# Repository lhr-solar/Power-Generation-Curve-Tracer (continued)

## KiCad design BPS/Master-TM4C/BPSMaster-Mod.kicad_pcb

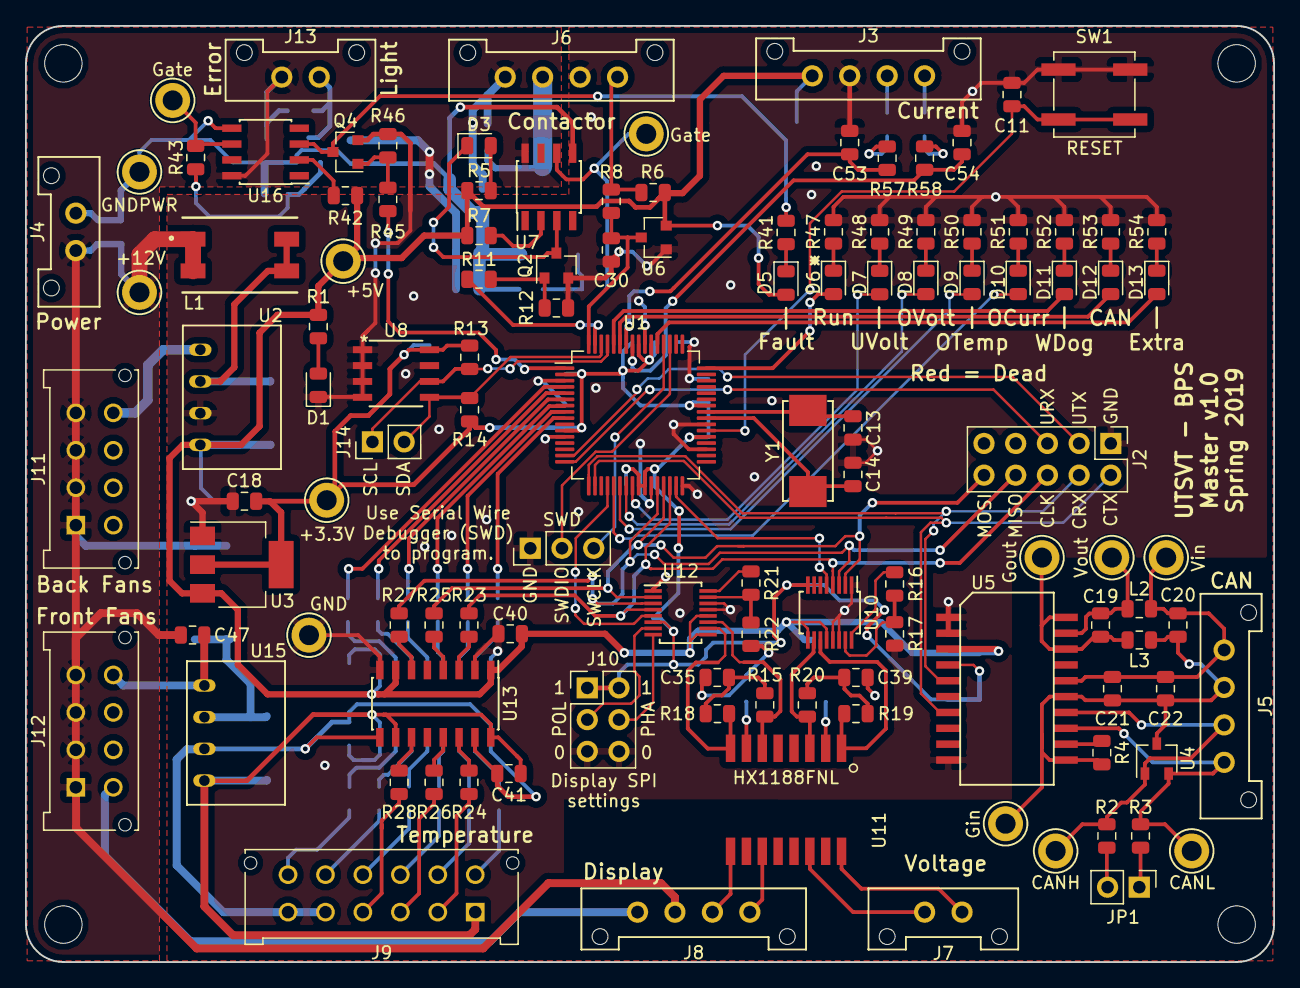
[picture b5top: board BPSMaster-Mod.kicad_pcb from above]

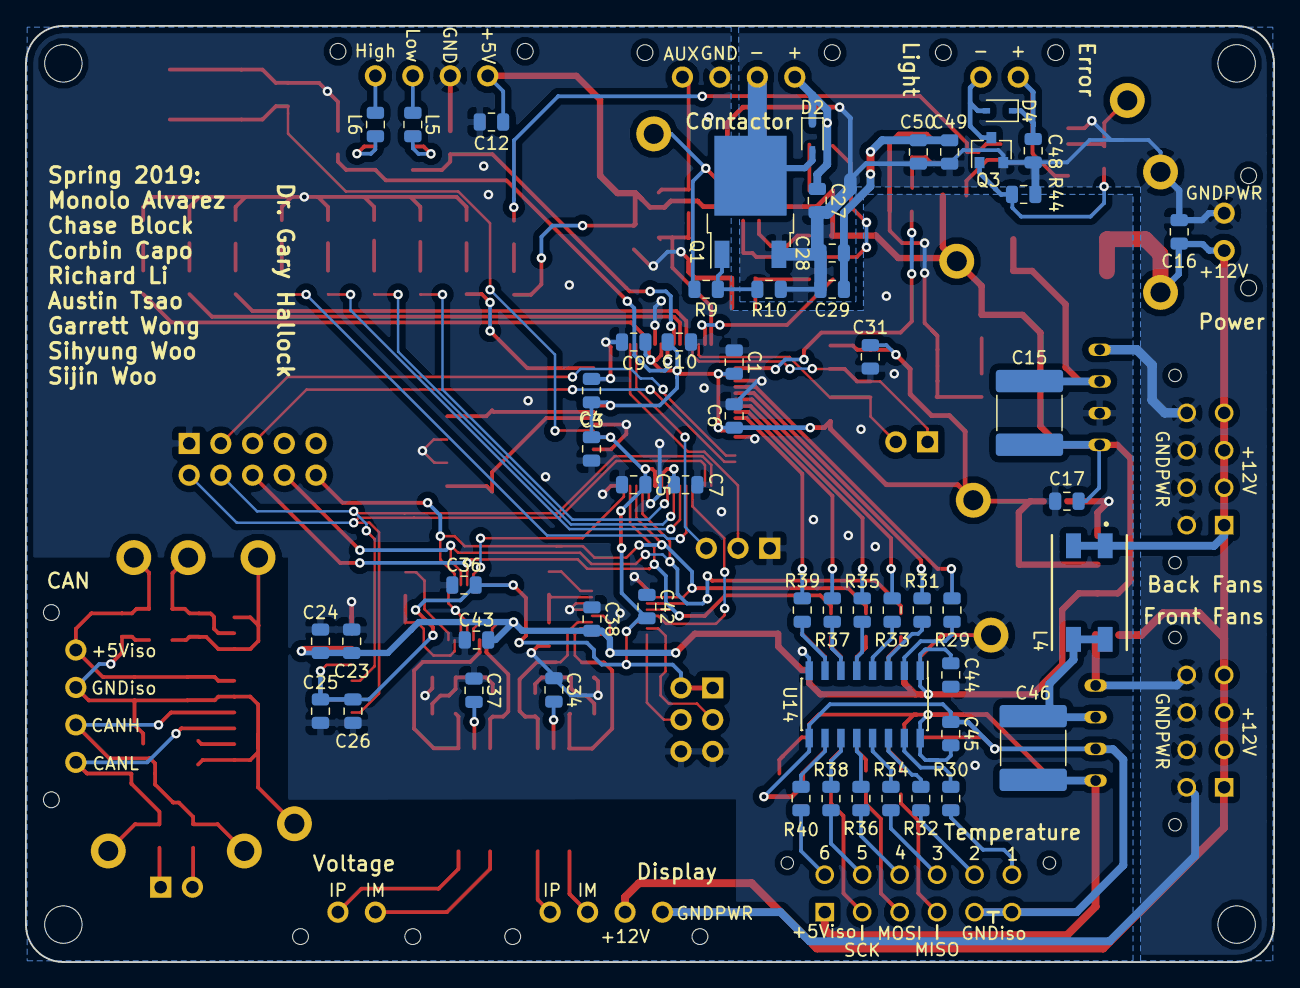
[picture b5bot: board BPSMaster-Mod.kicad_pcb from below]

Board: 2 copper layers, 100.0 x 75.0 mm, 176 parts (55 on the bottom side), 126 nets.

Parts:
C1, C3, C4, C5, C6, C9, C11, C12, C21, C24, C25, C29, C31, C36, C38, C40, C41, C42, C43, C44, C45, C50: 0.1uF; C_0805_2012Metric
C7, C16, C47: 4.7uF; C_0805_2012Metric
C10, C27, C30, C48, C53, C54: 1uF; C_0805_2012Metric
C13, C14: 6pF; C_0805_2012Metric
C15, C46: 470pF; C_2220_5650Metric
C17, C18, C20, C23, C28, C49: 10uF; C_0805_2012Metric
C19: 0.22uF; C_0805_2012Metric
C22, C26, C34, C35, C37, C39: 0.01uF; C_0805_2012Metric
D1: PowerOn; LED_0805_2012Metric
D2, D4: 1N4148WS; D_SOD-323
D3: ContactorEn; LED_0805_2012Metric
D5: Fault; LED_0805_2012Metric
D6: Heartbeat; LED_0805_2012Metric
D7: UVolt; LED_0805_2012Metric
D8: OVolt; LED_0805_2012Metric
D9: OTemp; LED_0805_2012Metric
D10: OCurr; LED_0805_2012Metric
D11: WDError; LED_0805_2012Metric
D12: CANError; LED_0805_2012Metric
D13: Extra; LED_0805_2012Metric
J1: SWD; PinHeader_1x03_P2.54mm_Vertical
J2: Logic Analyzer; PinHeader_2x05_P2.54mm_Vertical
J3: CurrentSlaveConnector; Molex_MicroFit3.0_1x4xP3.00mm_PolarizingPeg_Vertical
J4: CarPowerConnector; Molex_MicroFit3.0_1x2xP3.00mm_PolarizingPeg_Vertical
J5: CAN_Out; Molex_MicroFit3.0_1x4xP3.00mm_PolarizingPeg_Vertical
J6: ContactorConnector; Molex_MicroFit3.0_1x4xP3.00mm_PolarizingPeg_Vertical
J7: VoltageSlaveConnector; Molex_MicroFit3.0_1x2xP3.00mm_PolarizingPeg_Vertical
J8: DisplayConnector; Molex_MicroFit3.0_1x4xP3.00mm_PolarizingPeg_Vertical
J9: TempSlaveConnector; Molex_MicroFit3.0_2x6xP3.00mm_PolarizingPeg_Vertical
J10: DisplayJumper; PinHeader_2x03_P2.54mm_Vertical
J11: FrontFans; Molex_MicroFit3.0_2x4xP3.00mm_PolarizingPeg_Vertical
J12: BackFans; Molex_MicroFit3.0_2x4xP3.00mm_PolarizingPeg_Vertical
J13: ErrorLightConnector; Molex_MicroFit3.0_1x2xP3.00mm_PolarizingPeg_Vertical
J14: Conn_01x03; PinHeader_1x02_P2.54mm_Vertical
JP1: Termination Resistors; PinHeader_1x02_P2.54mm_Vertical
L1, L4: 10uH; SRF0905A
L2, L3: 2kH; L_0805_2012Metric
L5, L6: 600; L_0805_2012Metric
MH1, MH2, MH3, MH4: MountingHole; MountingHole_3mm
Q1: VND5N07-E; TO-252-2
Q2, Q3, Q4: NTR4003NT1G; SOT-23
R1, R5: 1.5k; R_0805_2012Metric
R2, R3: 60; R_0805_2012Metric
R4, R9, R11, R43, R45: 0; R_0805_2012Metric
R6, R13, R14: 4.7k; R_0805_2012Metric
R7, R42: 470; R_0805_2012Metric
R8: 1k; R_0805_2012Metric
R10, R12, R44, R46: 10k; R_0805_2012Metric
R15, R18, R19, R20: 49.9; R_0805_2012Metric
R16, R21: 806; R_0805_2012Metric
R17, R22: 1.21k; R_0805_2012Metric
R23, R24, R25, R26, R27, R28, R29, R30, R31, R32, R33, R34, R35, R36, R37, R38, R39, R40: 50; R_0805_2012Metric
R41: 1.6k; R_0805_2012Metric
R47: 680; R_0805_2012Metric
R48, R49, R50, R51, R52, R53, R54: 750; R_0805_2012Metric
R57, R58: 220k; R_0805_2012Metric
SW1: B3SL-1002P; SW_SPST_B3SL-1002P
TP1: +12V_TP; TestPoint_Keystone_5005-5009_Compact
TP2: +5V_TP; TestPoint_Keystone_5005-5009_Compact
TP3: GND_TP; TestPoint_Keystone_5005-5009_Compact
TP4: +3.3V_TP; TestPoint_Keystone_5005-5009_Compact
TP5: CAN_ISO_Vout; TestPoint_Keystone_5005-5009_Compact
TP6: CAN_ISO_Vin; TestPoint_Keystone_5005-5009_Compact
TP7: CAN_ISO_GndIn; TestPoint_Keystone_5005-5009_Compact
TP8: CAN_ISO_GndOut; TestPoint_Keystone_5005-5009_Compact
TP9: CAN_H; TestPoint_Keystone_5005-5009_Compact
TP12: CAN_L; TestPoint_Keystone_5005-5009_Compact
TP13: ContactorGate_TP; TestPoint_Keystone_5005-5009_Compact
TP14: StrobeLightGate_TP; TestPoint_Keystone_5005-5009_Compact
TP15: GNDPWR_TP; TestPoint_Keystone_5005-5009_Compact
U1: TM4C123GH6PM; LQFP-64_10x10mm_P0.5mm
U2, U15: RI3-1205S; RI3_DC_Converter
U3: NCP1117-3.3_SOT223; SOT-223-3_TabPin2
U4: CDSOT23-T24CAN; SOT-23W
U5: ADM3055E; SOIC-20W_7.5x15.4mm_Pitch1.27mm
U6: BAS70-04; SOT-23
U7, U16: SI8261ABC-IS; SOIC-8_3.9x4.9mm_P1.27mm
U8: M24128; M24128-BRMN6P
U10, U12: LTC6820; MSOP-16_3x4mm_P0.5mm
U11: HX1188FNL; HXXXX
U13: Si8641EC-B-IS1; SOIC-16_3.9x9.9mm_P1.27mm
U14: SI8660EC-B-IS1; SOIC-16_3.9x9.9mm_P1.27mm
Y1: NX8045GB-8.000M-STD-CSJ-1

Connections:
+3V3: C1.1, C3.1, C4.1, C5.1, C6.1, C7.1, C9.1, C10.1, C18.1, C25.1, C26.1, C31.1, C36.1, C42.1, J10.1, J10.2, R13.1, R14.1, TP4.1, U1.2, U1.11, U1.25, U1.26, U1.37, U1.42, U1.54, U1.56, U3.2, U5.4, U8.8, U10.6, U10.7, U10.8, U12.6
+5V: C12.2, C15.2, C17.1, C23.1, C24.1, C38.1, C40.1, C43.1, C44.1, D5.2, J3.1, R1.1, R5.1, R6.2, R7.2, R42.2, TP2.1, U2.4, U3.3, U5.3, U6.2, U10.9, U10.12, U12.9, U12.12, U13.1, U13.7, U14.1
+5VL: C41.1, C45.1, C46.2, J9.1, U13.10, U13.16, U14.16, U15.4
+12V: C16.1, C27.2, C28.1, C29.1, C47.1, C48.2, C49.1, C50.1, D2.1, D4.1, J4.1, J6.1, J8.3, J11.1, J11.2, J11.3, J11.4, J12.1, J12.2, J12.3, J12.4, J13.1, L1.1, L1.2, L4.1, L4.2, TP1.1, U7.8, U16.8
/AIN10: C53.1, R57.2, U1.58
/AIN11: C54.1, R58.2, U1.57
/CAN1_RX: J2.4, U1.17, U5.5
/CAN1_TX: J2.2, U1.18, U5.7
/CAN/CAN_H: J5.3, R2.2, TP9.1, U4.1, U5.14
/CAN/CAN_L: J5.4, R3.2, TP12.1, U4.2, U5.13
/CAN/RSlope: R4.1, U5.12
/CAN/TERM_H: JP1.2, R2.1
/CAN/TERM_L: JP1.1, R3.1
/Contactor Driver/CONTACTOR_V-: D2.2, J6.2, Q1.2
/DISPLAY_CS: U1.20, U12.5
/FAULT: R45.2, U1.1
/I2C3_SCL: J14.1, R13.2, U1.61, U8.6
/I2C3_SDA: J14.2, R14.2, U1.62, U8.5
/LTC6811_CS: U1.31, U10.5
/NRST: C11.1, SW1.1, U1.38
/OSC_IN: C14.1, U1.40, Y1.2
/OSC_OUT: C13.1, U1.41, Y1.1
/PA4: D10.2, U1.21
/PA5: D9.2, U1.22
/PA6: D8.2, U1.23
/PA7: D7.2, U1.24
/PD2: R11.2, U1.63
/PD3: C30.1, R8.1, U1.64, U6.3
/PD6: D13.2, U1.53
/PE4: D12.2, U1.59
/PE5: D11.2, U1.60
/RUN: D6.2, U1.48
/SPI1_CLK: J2.6, R23.2, U1.30, U10.4, U12.4
/SPI1_MISO: J2.8, R27.2, U1.28, U10.3, U12.3
/SPI1_MOSI: J2.10, R25.2, U1.29, U10.2, U12.2
/SPI/CS1: J9.12, R30.1
/SPI/CS2: J9.11, R32.1
/SPI/CS3: J9.10, R34.1
/SPI/CS4: J9.9, R36.1
/SPI/CS5: J9.8, R38.1
/SPI/CS6: J9.7, R40.1
/SPI/DISP_IM: R18.1, U11.8, U12.10
/SPI/DISP_IP: R15.1, U11.6, U12.11
/SPI/DISP_PHA: J10.4, U12.8
/SPI/DISP_POL: J10.3, U12.7
/SPI/VOLT_IM: R20.1, U10.10, U11.3
/SPI/VOLT_IP: R19.1, U10.11, U11.1
/SWCLK: J1.3, U1.52
/SWDIO: J1.2, U1.51
/TEMP_CS1: R29.1, U1.4
/TEMP_CS2: R31.1, U1.5
/TEMP_CS3: R33.1, U1.6
/TEMP_CS4: R35.1, U1.7
/TEMP_CS5: R37.1, U1.8
/TEMP_CS6: R39.1, U1.9
/UART1_RX: J2.5, U1.16
/UART1_TX: J2.3, U1.15
GND: C1.2, C3.2, C4.2, C5.2, C6.2, C7.2, C9.2, C10.2, C11.2, C12.1, C13.2, C14.2, C17.2, C18.2, C23.2, C24.2, C25.2, C26.2, C30.2, C31.2, C34.2, C35.2, C36.2, C37.2, C38.2, C39.2, C40.2, C42.2, C43.2, C44.2, C53.2, C54.2, D1.1, J1.1, J2.1, J3.2, J6.3, J10.5, J10.6, Q2.2, Q4.2, R12.2, R17.1, R22.1, R46.2, R47.2, R48.2, R49.2, R50.2, R51.2, R52.2, R53.2, R54.2, SW1.2, TP3.1, U1.3, U1.12, U1.27, U1.32, U1.35, U1.39, U1.55, U2.3, U3.1, U5.1, U5.2, U5.10, U6.1, U8.1, U8.2, U8.3, U8.4, U8.7, U10.1, U10.13, U10.14, U12.1, U12.13, U12.14, U13.2, U13.8, U14.8
GNDPWR: C16.2, C27.1, C28.2, C29.2, C47.2, C48.1, C49.2, C50.2, J4.2, J8.4, J11.5, J11.6, J11.7, J11.8, J12.5, J12.6, J12.7, J12.8, Q1.3, Q3.2, R10.2, R44.2, TP15.1, U2.1, U7.5, U15.1, U16.5
GND_A: C41.2, C45.2, J9.5, J9.6, U13.9, U13.15, U14.9, U15.3
unnamed: C15.1, L1.3, L1.4, U2.2
unnamed: C19.1, L2.2, TP5.1, U5.19
unnamed: C19.2, L3.2, TP8.1, U5.18, U5.20
unnamed: C20.1, C21.1, C22.1, J5.1, L2.1, TP6.1, U5.16
unnamed: C20.2, C21.2, C22.2, J5.2, L3.1, R4.2, TP7.1, U4.3, U5.11, U5.15
unnamed: C34.1, U11.7
unnamed: C35.1, R15.2, R18.2
unnamed: C37.1, U11.2
unnamed: C39.1, R19.2, R20.2
unnamed: C46.1, L4.3, L4.4, U15.2
unnamed: D1.2, R1.2
unnamed: D3.1, Q2.3, U7.3
unnamed: D3.2, R5.2
unnamed: D4.2, J13.2, Q3.3
unnamed: D5.1, R41.1
unnamed: D6.1, R47.1
unnamed: D7.1, R48.1
unnamed: D8.1, R49.1
unnamed: D9.1, R50.1
unnamed: D10.1, R51.1
unnamed: D11.1, R52.1
unnamed: D12.1, R53.1
unnamed: D13.1, R54.1
unnamed: J3.3, L5.1
unnamed: J3.4, L6.1
unnamed: J6.4, R6.1, R8.2
unnamed: J7.1, U11.16
unnamed: J7.2, U11.14
unnamed: J8.1, U11.11
unnamed: J8.2, U11.9
unnamed: J9.2, R24.2
unnamed: J9.3, R26.2
unnamed: J9.4, R28.2
unnamed: L5.2, R57.1
unnamed: L6.2, R58.1
unnamed: Q1.1, R9.1, R10.1
unnamed: Q2.1, R11.1, R12.1
unnamed: Q3.1, R43.1, R44.1
unnamed: Q4.1, R45.1, R46.1
unnamed: Q4.3, R41.2, U16.3
unnamed: R7.1, U7.2
unnamed: R9.2, TP13.1, U7.6
unnamed: R16.1, R17.2, U10.15
unnamed: R16.2, U10.16
unnamed: R21.1, R22.2, U12.15
unnamed: R21.2, U12.16
unnamed: R23.1, U13.3
unnamed: R24.1, U13.14
unnamed: R25.1, U13.4
unnamed: R26.1, U13.13
unnamed: R27.1, U13.6
unnamed: R28.1, U13.11
unnamed: R29.2, U14.2
unnamed: R30.2, U14.15
unnamed: R31.2, U14.3
unnamed: R32.2, U14.14
unnamed: R33.2, U14.4
unnamed: R34.2, U14.13
unnamed: R35.2, U14.5
unnamed: R36.2, U14.12
unnamed: R37.2, U14.6
unnamed: R38.2, U14.11
unnamed: R39.2, U14.7
unnamed: R40.2, U14.10
unnamed: R42.1, U16.2
unnamed: R43.2, TP14.1, U16.6

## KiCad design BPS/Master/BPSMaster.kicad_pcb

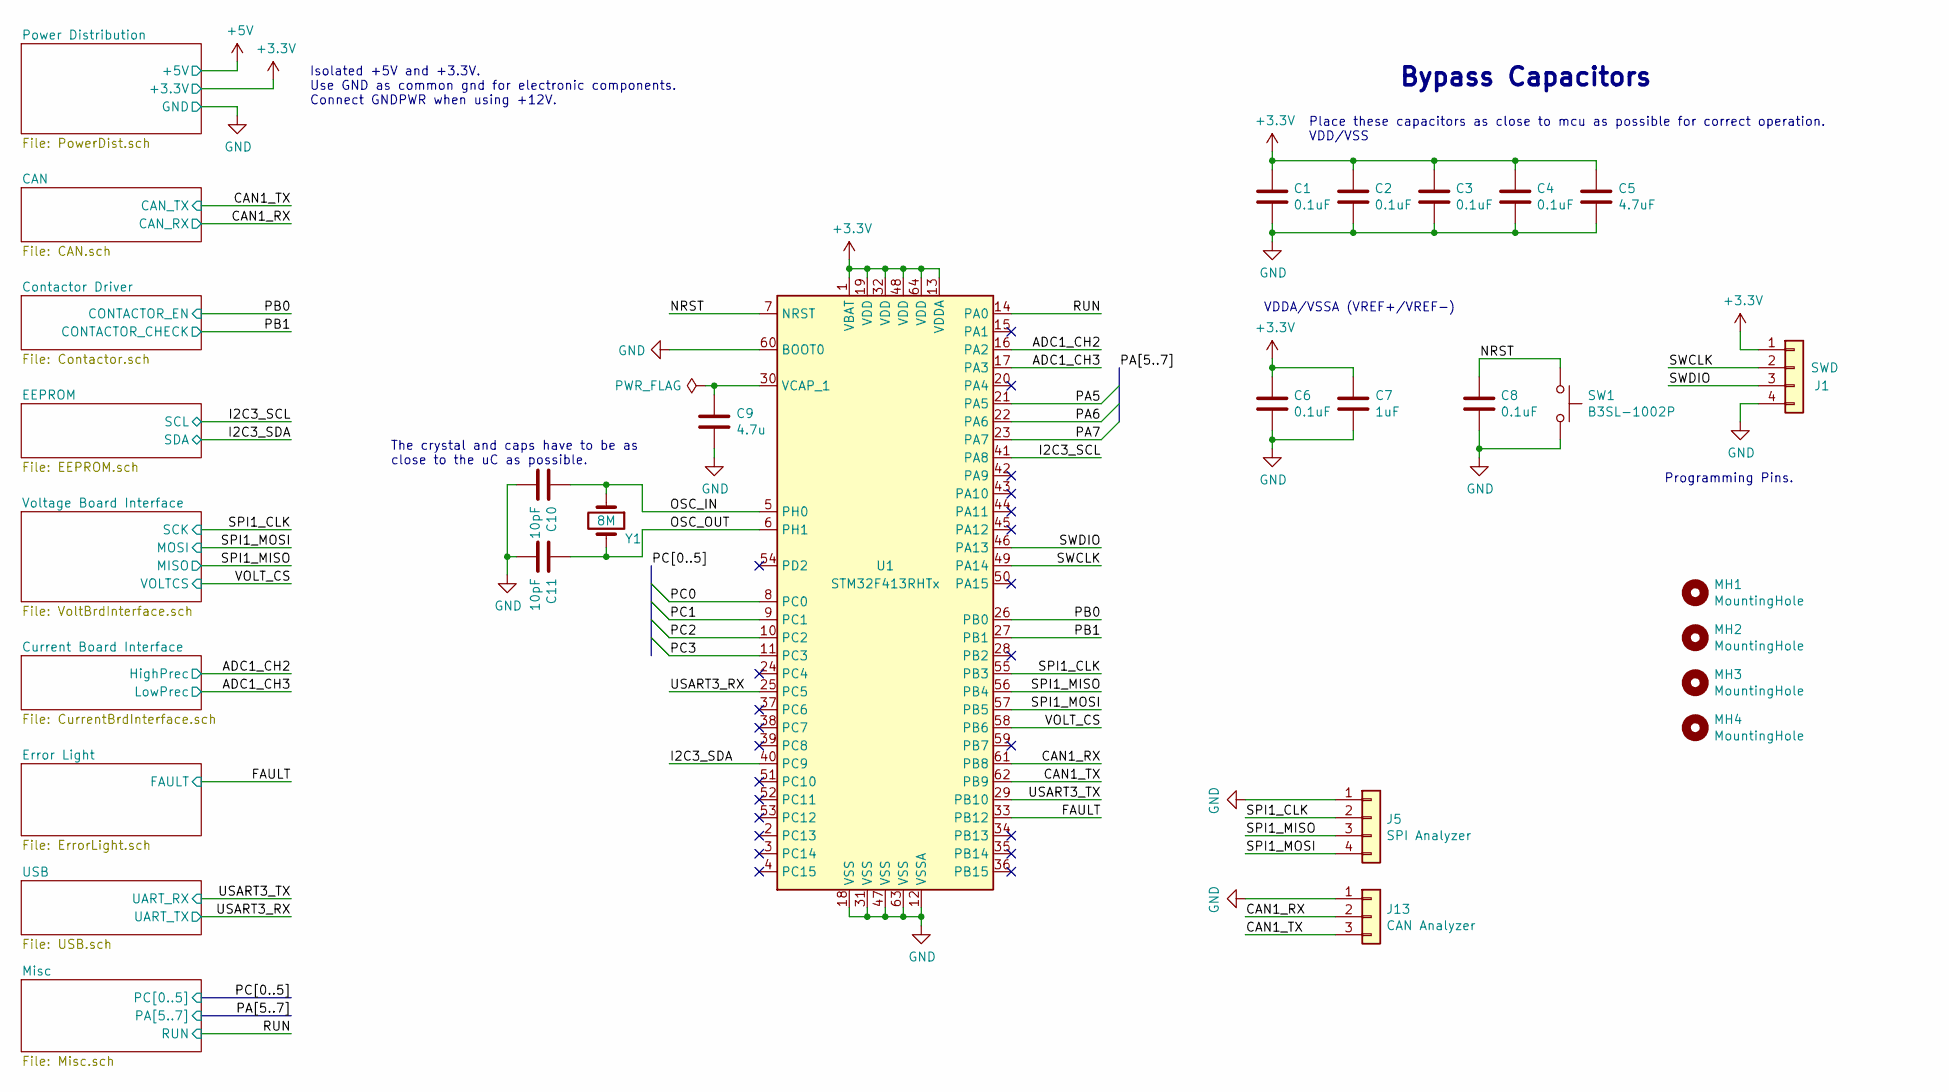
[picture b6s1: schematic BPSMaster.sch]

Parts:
C1, C2, C3, C4, C6, C8: 0.1uF; C_0805_2012Metric
C5: 4.7uF; C_0805_2012Metric
C7: 1uF; C_0805_2012Metric
C9: 4.7u; C_0805_2012Metric
C10, C11: 10pF; C_0805_2012Metric
J1: SWD; PinHeader_1x04_P2.54mm_Vertical
J5: SPI Analyzer; PinHeader_1x04_P2.54mm_Vertical
J13: CAN Analyzer; PinHeader_1x03_P2.54mm_Vertical
MH1, MH2, MH3, MH4: MountingHole; MountingHole_3mm
SW1: B3SL-1002P; SW_SPST_B3SL-1002P
U1: STM32F413RHTx; LQFP-64_10x10mm_P0.5mm
Y1: 8M; Crystal_SMD_TXC_7A-2Pin_5x3.2mm

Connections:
+3V3: C1.1, C2.1, C3.1, C4.1, C5.1, C6.1, C7.1, J1.1, U1.1 (VBAT), U1.13 (VDDA), U1.19 (VDD), U1.32 (VDD), U1.48 (VDD), U1.64 (VDD); also elsewhere on the board
/ADC1_CH2: U1.16 (PA2); also elsewhere on the board
/ADC1_CH3: U1.17 (PA3); also elsewhere on the board
/CAN1_RX: J13.2, U1.61 (PB8); also elsewhere on the board
/CAN1_TX: J13.3, U1.62 (PB9); also elsewhere on the board
/FAULT: U1.33 (PB12); also elsewhere on the board
/I2C3_SCL: U1.41 (PA8); also elsewhere on the board
/I2C3_SDA: U1.40 (PC9); also elsewhere on the board
/NRST: C8.1, SW1.1, U1.7 (NRST)
/OSC_IN: C10.1, U1.5 (PH0), Y1.1
/OSC_OUT: C11.1, U1.6 (PH1), Y1.2
/PA5: U1.21 (PA5); also elsewhere on the board
/PA6: U1.22 (PA6); also elsewhere on the board
/PA7: U1.23 (PA7); also elsewhere on the board
/PB0: U1.26 (PB0); also elsewhere on the board
/PB1: U1.27 (PB1); also elsewhere on the board
/PC0: U1.8 (PC0); also elsewhere on the board
/PC1: U1.9 (PC1); also elsewhere on the board
/PC2: U1.10 (PC2); also elsewhere on the board
/PC3: U1.11 (PC3); also elsewhere on the board
/RUN: U1.14 (PA0); also elsewhere on the board
/SPI1_CLK: J5.2, U1.55 (PB3); also elsewhere on the board
/SPI1_MISO: J5.3, U1.56 (PB4); also elsewhere on the board
/SPI1_MOSI: J5.4, U1.57 (PB5); also elsewhere on the board
/SWCLK: J1.2, U1.49 (PA14)
/SWDIO: J1.3, U1.46 (PA13)
/USART3_RX: U1.25 (PC5); also elsewhere on the board
/USART3_TX: U1.29 (PB10); also elsewhere on the board
/VOLT_CS: U1.58 (PB6); also elsewhere on the board
GND: C1.2, C2.2, C3.2, C4.2, C5.2, C6.2, C7.2, C8.2, C9.2, C10.2, C11.2, J1.4, J5.1, J13.1, SW1.2, U1.12 (VSSA), U1.18 (VSS), U1.31 (VSS), U1.47 (VSS), U1.60 (BOOT0), U1.63 (VSS); also elsewhere on the board
unnamed: C9.1, U1.30 (VCAP_1)

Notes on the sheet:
Place these capacitors as close to mcu as possible for correct operation. VDD/VSS
VDDA/VSSA (VREF+/VREF-)
Isolated +5V and +3.3V. Use GND as common gnd for electronic components. Connect GNDPWR when using +12V.
The crystal and caps have to be as close to the uC as possible.
Programming Pins.
Bypass Capacitors

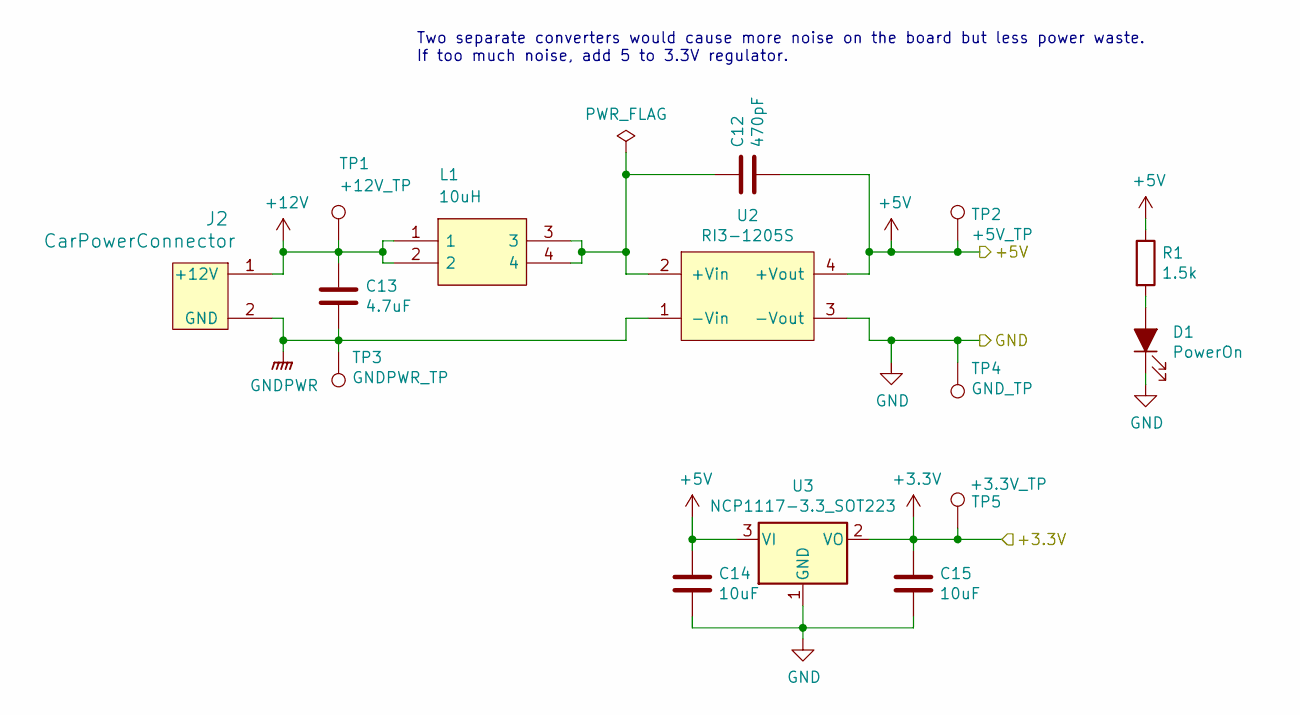
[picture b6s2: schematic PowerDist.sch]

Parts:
C12: 470pF; C_2220_5650Metric; Rating 4kV
C13: 4.7uF; C_0805_2012Metric
C14, C15: 10uF; C_0805_2012Metric
D1: PowerOn; LED_0805_2012Metric
J2: CarPowerConnector; Molex_MicroFit3.0_1x2xP3.00mm_PolarizingPeg_Vertical
L1: 10uH; SRF0905A
R1: 1.5k; R_0805_2012Metric
TP1: +12V_TP; TestPoint_Keystone_5005-5009_Compact
TP2: +5V_TP; TestPoint_Keystone_5005-5009_Compact
TP3: GNDPWR_TP; TestPoint_Keystone_5005-5009_Compact
TP4: GND_TP; TestPoint_Keystone_5005-5009_Compact
TP5: +3.3V_TP; TestPoint_Keystone_5005-5009_Compact
U2: RI3-1205S; RI3_DC_Converter
U3: NCP1117-3.3_SOT223; SOT-223-3_TabPin2

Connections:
+3V3: C15.1, TP5.1, U3.2 (VO); also elsewhere on the board
+5V: C12.2, C14.1, R1.1, TP2.1, U2.4 (+Vout), U3.3 (VI); also elsewhere on the board
+12V: C13.1, J2.1 (+12V), L1.1, L1.2, TP1.1; also elsewhere on the board
GND: C14.2, C15.2, D1.1 (K), TP4.1, U2.3 (-Vout), U3.1 (GND); also elsewhere on the board
GNDPWR: C13.2, J2.2 (GND), TP3.1, U2.1 (-Vin); also elsewhere on the board
unnamed: C12.1, L1.3, L1.4, U2.2 (+Vin)
unnamed: D1.2 (A), R1.2

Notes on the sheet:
Two separate converters would cause more noise on the board but less power waste. If too much noise, add 5 to 3.3V regulator.

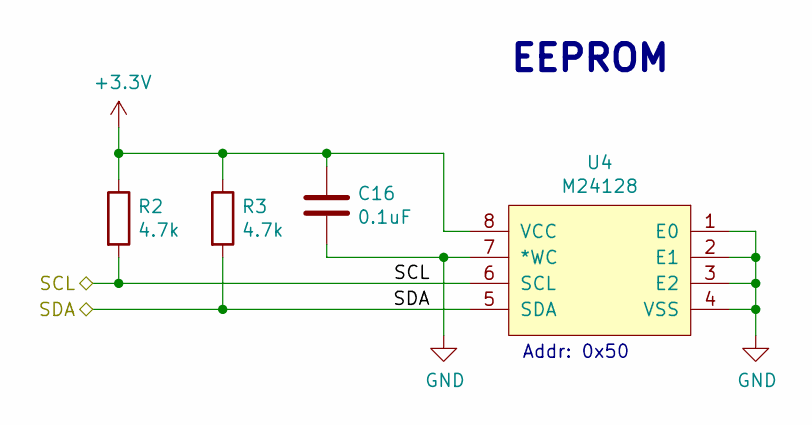
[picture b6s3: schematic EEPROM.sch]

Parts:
C16: 0.1uF; C_0805_2012Metric
R2, R3: 4.7k; R_0805_2012Metric
U4: M24128; M24128-BRMN6P

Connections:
+3V3: C16.1, R2.1, R3.1, U4.8 (VCC); also elsewhere on the board
/I2C3_SCL: R2.2, U4.6 (SCL); also elsewhere on the board
/I2C3_SDA: R3.2, U4.5 (SDA); also elsewhere on the board
GND: C16.2, U4.1 (E0), U4.2 (E1), U4.3 (E2), U4.4 (VSS), U4.7 (*WC); also elsewhere on the board

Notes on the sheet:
EEPROM
Addr: 0x50

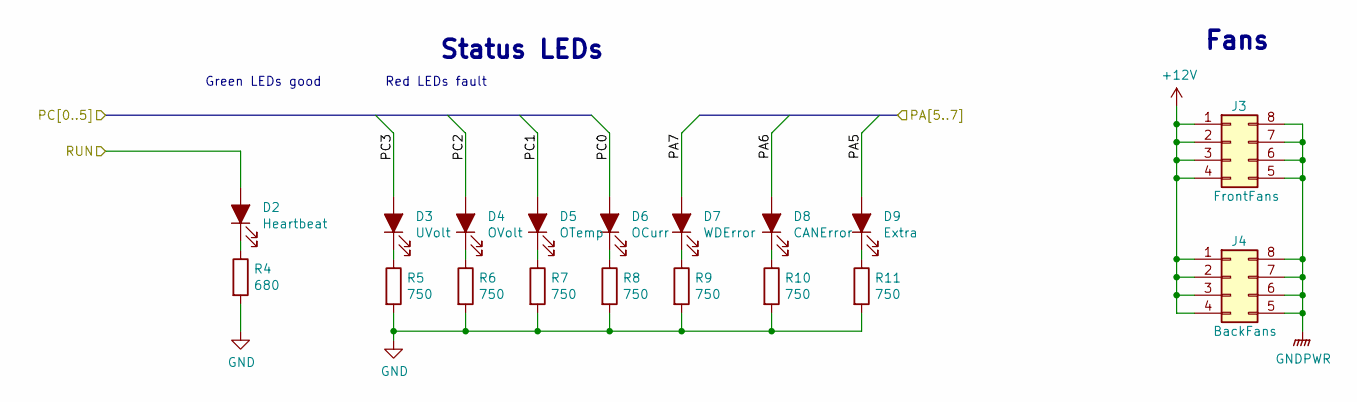
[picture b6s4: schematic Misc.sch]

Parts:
D2: Heartbeat; LED_0805_2012Metric
D3: UVolt; LED_0805_2012Metric
D4: OVolt; LED_0805_2012Metric
D5: OTemp; LED_0805_2012Metric
D6: OCurr; LED_0805_2012Metric
D7: WDError; LED_0805_2012Metric
D8: CANError; LED_0805_2012Metric
D9: Extra; LED_0805_2012Metric
J3: FrontFans; Molex_MicroFit3.0_2x4xP3.00mm_PolarizingPeg_Vertical
J4: BackFans; Molex_MicroFit3.0_2x4xP3.00mm_PolarizingPeg_Vertical
R4: 680; R_0805_2012Metric
R5, R6, R7, R8, R9, R10, R11: 750; R_0805_2012Metric

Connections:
+12V: J3.1, J3.2, J3.3, J3.4, J4.1, J4.2, J4.3, J4.4; also elsewhere on the board
/PA5: D9.2 (A); also elsewhere on the board
/PA6: D8.2 (A); also elsewhere on the board
/PA7: D7.2 (A); also elsewhere on the board
/PC0: D6.2 (A); also elsewhere on the board
/PC1: D5.2 (A); also elsewhere on the board
/PC2: D4.2 (A); also elsewhere on the board
/PC3: D3.2 (A); also elsewhere on the board
/RUN: D2.2 (A); also elsewhere on the board
GND: R4.2, R5.2, R6.2, R7.2, R8.2, R9.2, R10.2, R11.2; also elsewhere on the board
GNDPWR: J3.5, J3.6, J3.7, J3.8, J4.5, J4.6, J4.7, J4.8; also elsewhere on the board
unnamed: D2.1 (K), R4.1
unnamed: D3.1 (K), R5.1
unnamed: D4.1 (K), R6.1
unnamed: D5.1 (K), R7.1
unnamed: D6.1 (K), R8.1
unnamed: D7.1 (K), R9.1
unnamed: D8.1 (K), R10.1
unnamed: D9.1 (K), R11.1

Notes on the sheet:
Fans
Green LEDs good
Red LEDs fault
Status LEDs

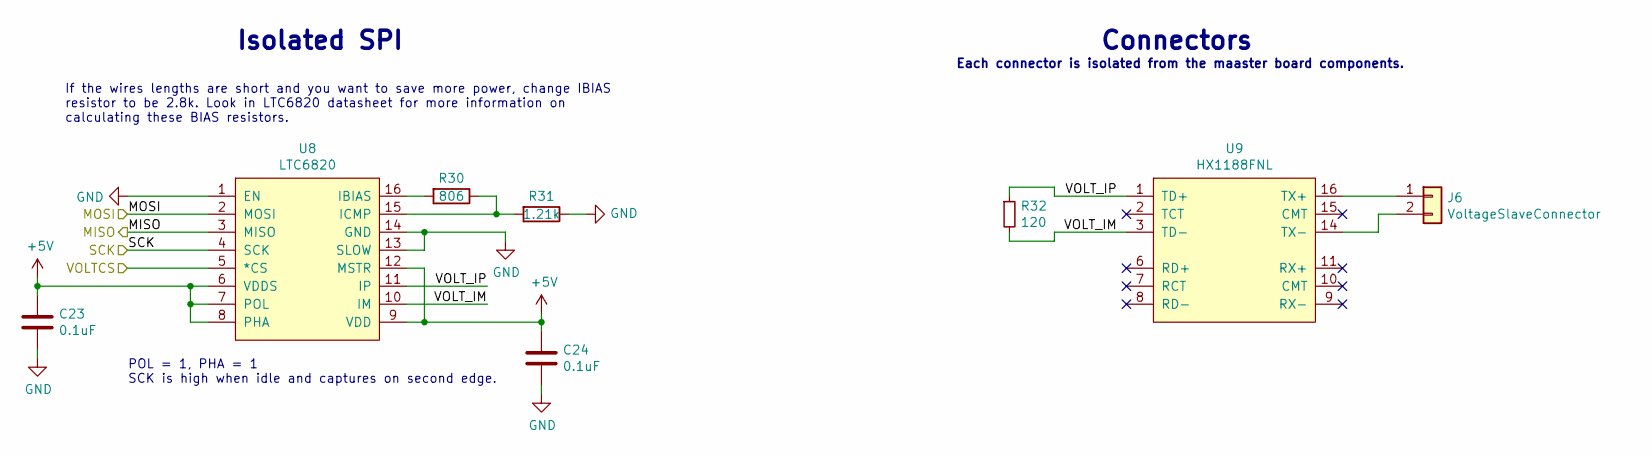
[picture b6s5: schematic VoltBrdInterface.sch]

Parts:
C23, C24: 0.1uF; C_0805_2012Metric
J6: VoltageSlaveConnector; Molex_MicroFit3.0_1x2xP3.00mm_PolarizingPeg_Vertical
R30: 806; R_0805_2012Metric
R31: 1.21k; R_0805_2012Metric
R32: 120; R_0805_2012Metric
U8: LTC6820; MSOP-16_3x4mm_P0.5mm
U9: HX1188FNL; HXXXX

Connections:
+5V: C23.1, C24.1, U8.6 (VDDS), U8.7 (POL), U8.8 (PHA), U8.9 (VDD), U8.12 (MSTR); also elsewhere on the board
/SPI1_CLK: U8.4 (SCK); also elsewhere on the board
/SPI1_MISO: U8.3 (MISO); also elsewhere on the board
/SPI1_MOSI: U8.2 (MOSI); also elsewhere on the board
/VOLT_CS: U8.5 (*CS); also elsewhere on the board
/Voltage Board Interface/VOLT_IM: R32.2, U8.10 (IM), U9.3 (TD-)
/Voltage Board Interface/VOLT_IP: R32.1, U8.11 (IP), U9.1 (TD+)
GND: C23.2, C24.2, R31.1, U8.1 (EN), U8.13 (SLOW), U8.14 (GND); also elsewhere on the board
unnamed: J6.1, U9.16 (TX+)
unnamed: J6.2, U9.14 (TX-)
unnamed: R30.1, R31.2, U8.15 (ICMP)
unnamed: R30.2, U8.16 (IBIAS)

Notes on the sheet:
POL = 1, PHA = 1 SCK is high when idle and captures on second edge.
If the wires lengths are short and you want to save more power, change IBIAS resistor to be 2.8k. Look in LTC6820 datasheet for more information on calculating these BIAS resistors.
Connectors
Each connector is isolated from the maaster board components.
Isolated SPI

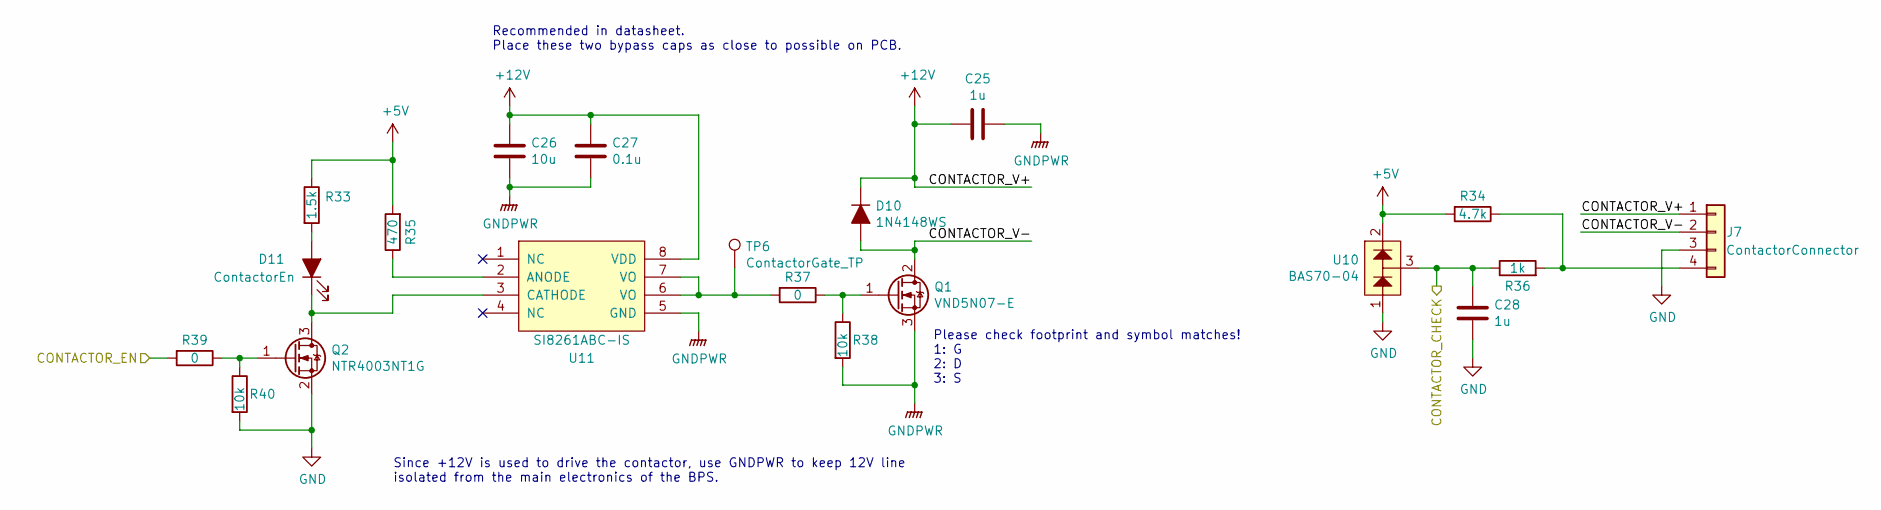
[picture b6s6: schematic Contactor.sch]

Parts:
C25, C28: 1u; C_0805_2012Metric
C26: 10u; C_0805_2012Metric
C27: 0.1u; C_0805_2012Metric
D10: 1N4148WS; D_SOD-323
D11: ContactorEn; LED_0805_2012Metric
J7: ContactorConnector; Molex_MicroFit3.0_1x4xP3.00mm_PolarizingPeg_Vertical
Q1: VND5N07-E; TO-252-2
Q2: NTR4003NT1G; SOT-23
R33: 1.5k; R_0805_2012Metric
R34: 4.7k; R_0805_2012Metric
R35: 470; R_0805_2012Metric
R36: 1k; R_0805_2012Metric
R37, R39: 0; R_0805_2012Metric
R38, R40: 10k; R_0805_2012Metric
TP6: ContactorGate_TP; TestPoint_Keystone_5005-5009_Compact
U10: BAS70-04; SOT-23
U11: SI8261ABC-IS; SOIC-8_3.9x4.9mm_P1.27mm

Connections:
+5V: R33.1, R34.2, R35.2, U10.2; also elsewhere on the board
+12V: C25.2, C26.1, C27.1, D10.1 (K), J7.1, U11.8 (VDD); also elsewhere on the board
/Contactor Driver/CONTACTOR_V-: D10.2 (A), J7.2, Q1.2 (D)
/PB0: R39.2; also elsewhere on the board
/PB1: C28.1, R36.1, U10.3; also elsewhere on the board
GND: C28.2, J7.3, Q2.2 (S), R40.2, U10.1; also elsewhere on the board
GNDPWR: C25.1, C26.2, C27.2, Q1.3 (S), R38.2, U11.5 (GND); also elsewhere on the board
unnamed: D11.1 (K), Q2.3 (D), U11.3 (CATHODE)
unnamed: D11.2 (A), R33.2
unnamed: J7.4, R34.1, R36.2
unnamed: Q1.1 (G), R37.1, R38.1
unnamed: Q2.1 (G), R39.1, R40.1
unnamed: R35.1, U11.2 (ANODE)
unnamed: R37.2, TP6.1, U11.6 (VO), U11.7 (VO)

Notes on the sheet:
Since +12V is used to drive the contactor, use GNDPWR to keep 12V line isolated from the main electronics of the BPS.
Recommended in datasheet. Place these two bypass caps as close to possible on PCB.
Please check footprint and symbol matches! 1: G 2: D 3: S

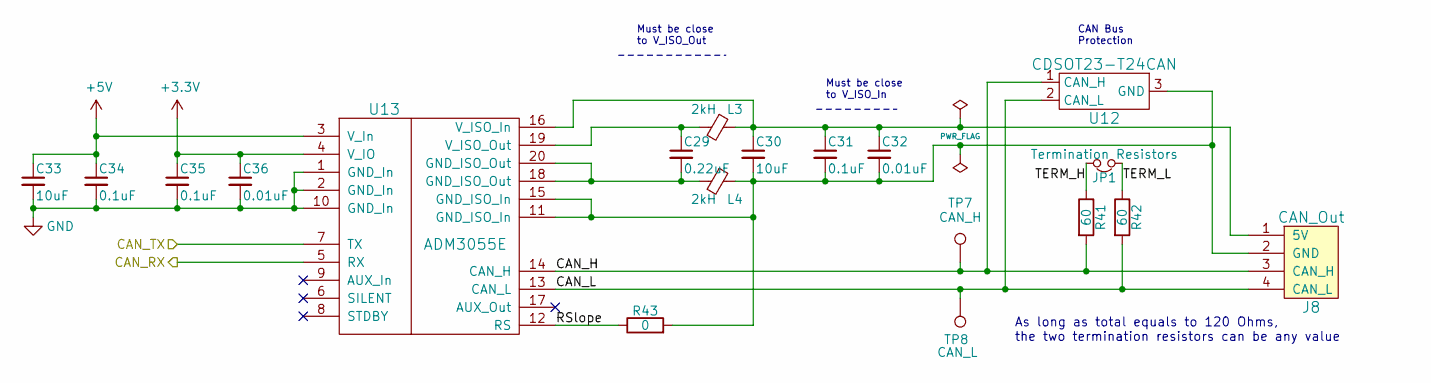
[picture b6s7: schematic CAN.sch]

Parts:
C29: 0.22uF; C_0805_2012Metric
C30, C33: 10uF; C_0805_2012Metric
C31, C34, C35: 0.1uF; C_0805_2012Metric
C32, C36: 0.01uF; C_0805_2012Metric
J8: CAN_Out; Molex_MicroFit3.0_1x4xP3.00mm_PolarizingPeg_Vertical
JP1: Termination Resistors; PinHeader_1x02_P2.54mm_Vertical
L3, L4: 2kH; L_0805_2012Metric
R41, R42: 60; R_0805_2012Metric
R43: 0; R_0805_2012Metric
TP7: CAN_H; TestPoint_Keystone_5005-5009_Compact
TP8: CAN_L; TestPoint_Keystone_5005-5009_Compact
U12: CDSOT23-T24CAN; SOT-23W
U13: ADM3055E; SOIC-20W_7.5x15.4mm_Pitch1.27mm

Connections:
+3V3: C35.1, C36.1, U13.4 (V_IO); also elsewhere on the board
+5V: C33.1, C34.1, U13.3 (V_In); also elsewhere on the board
/CAN1_RX: U13.5 (RX); also elsewhere on the board
/CAN1_TX: U13.7 (TX); also elsewhere on the board
/CAN/CAN_H: J8.3 (CAN_H), R41.2, TP7.1, U12.1 (CAN_H), U13.14 (CAN_H)
/CAN/CAN_L: J8.4 (CAN_L), R42.2, TP8.1, U12.2 (CAN_L), U13.13 (CAN_L)
/CAN/RSlope: R43.1, U13.12 (RS)
/CAN/TERM_H: JP1.2, R41.1
/CAN/TERM_L: JP1.1, R42.1
GND: C33.2, C34.2, C35.2, C36.2, U13.1 (GND_In), U13.2 (GND_In), U13.10 (GND_In); also elsewhere on the board
unnamed: C29.1, L3.2, U13.19 (V_ISO_Out)
unnamed: C29.2, L4.2, U13.18 (GND_ISO_Out), U13.20 (GND_ISO_Out)
unnamed: C30.1, C31.1, C32.1, J8.1 (5V), L3.1, U13.16 (V_ISO_In)
unnamed: C30.2, C31.2, C32.2, J8.2 (GND), L4.1, R43.2, U12.3 (GND), U13.11 (GND_ISO_In), U13.15 (GND_ISO_In)

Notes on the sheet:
Must be close to V_ISO_Out
Must be close to V_ISO_In
CAN Bus Protection
As long as total equals to 120 Ohms, the two termination resistors can be any value

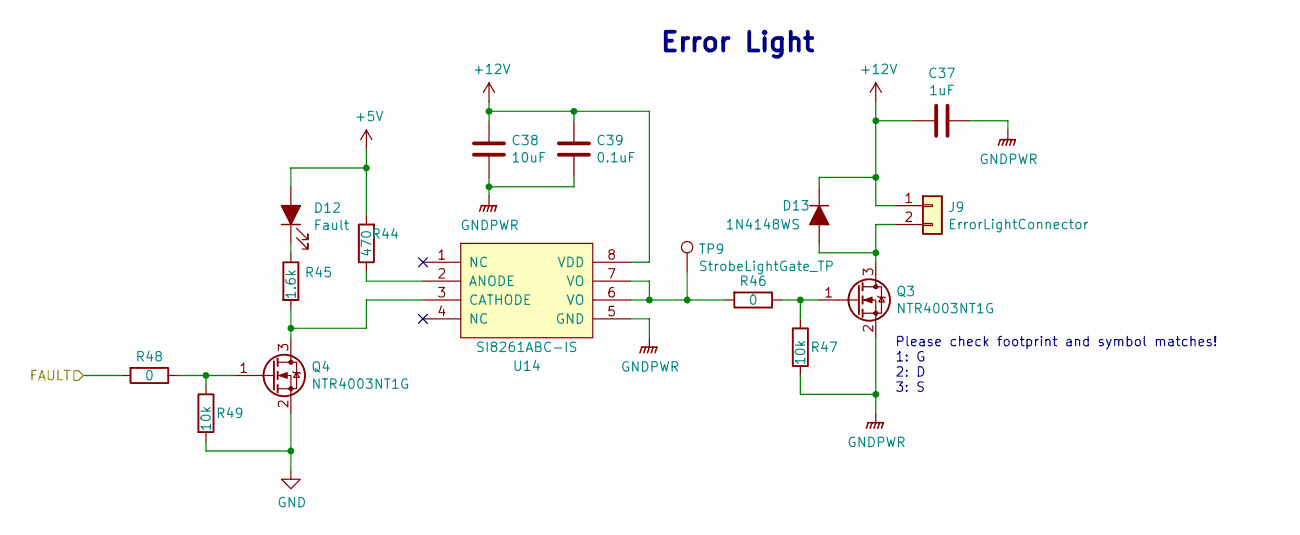
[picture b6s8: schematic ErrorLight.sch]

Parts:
C37: 1uF; C_0805_2012Metric
C38: 10uF; C_0805_2012Metric
C39: 0.1uF; C_0805_2012Metric
D12: Fault; LED_0805_2012Metric
D13: 1N4148WS; D_SOD-323
J9: ErrorLightConnector; Molex_MicroFit3.0_1x2xP3.00mm_PolarizingPeg_Vertical
Q3, Q4: NTR4003NT1G; SOT-23
R44: 470; R_0805_2012Metric
R45: 1.6k; R_0805_2012Metric
R46, R48: 0; R_0805_2012Metric
R47, R49: 10k; R_0805_2012Metric
TP9: StrobeLightGate_TP; TestPoint_Keystone_5005-5009_Compact
U14: SI8261ABC-IS; SOIC-8_3.9x4.9mm_P1.27mm

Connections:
+5V: D12.2 (A), R44.2; also elsewhere on the board
+12V: C37.2, C38.1, C39.1, D13.1 (K), J9.1, U14.8 (VDD); also elsewhere on the board
/FAULT: R48.2; also elsewhere on the board
GND: Q4.2 (S), R49.2; also elsewhere on the board
GNDPWR: C37.1, C38.2, C39.2, Q3.2 (S), R47.2, U14.5 (GND); also elsewhere on the board
unnamed: D12.1 (K), R45.1
unnamed: D13.2 (A), J9.2, Q3.3 (D)
unnamed: Q3.1 (G), R46.1, R47.1
unnamed: Q4.1 (G), R48.1, R49.1
unnamed: Q4.3 (D), R45.2, U14.3 (CATHODE)
unnamed: R44.1, U14.2 (ANODE)
unnamed: R46.2, TP9.1, U14.6 (VO), U14.7 (VO)

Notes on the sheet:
Error Light
Please check footprint and symbol matches! 1: G 2: D 3: S

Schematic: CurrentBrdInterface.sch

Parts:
C40: 0.1uF; C_0805_2012Metric
C41, C42: 0.01u; C_0805_2012Metric
J10: CurrentSlaveConnector; Molex_MicroFit3.0_1x4xP3.00mm_PolarizingPeg_Vertical
L5, L6: 600; L_0805_2012Metric
R12, R13, R50, R51: 100; R_0805_2012Metric
U5: LTC6256; LTC6256CTS8-TRMPBF

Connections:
+3V3: R12.2, R13.2, U5.8 (V+); also elsewhere on the board
+5V: C40.2, J10.1; also elsewhere on the board
/ADC1_CH2: C41.1, R51.2; also elsewhere on the board
/ADC1_CH3: C42.2, R50.2; also elsewhere on the board
GND: C40.1, C41.2, C42.1, J10.2, U5.4 (V-); also elsewhere on the board
unnamed: J10.3, L5.1
unnamed: J10.4, L6.1
unnamed: L5.2, R12.1, U5.3 (+INA)
unnamed: L6.2, R13.1, U5.5 (+INB)
unnamed: R50.1, U5.1 (OUTA), U5.2 (-INA)
unnamed: R51.1, U5.6 (-INB), U5.7 (OUTB)

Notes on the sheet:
PA2 high precision hall effect sensor. PA3 low precision hall effect sensor.
Current Board
The ADC has low impedence so buffer op-amp will prevent weird measurement deviations.
Pull up resistors are for disconnections

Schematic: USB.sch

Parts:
C43: 4.7uF; C_0805_2012Metric
C44: 0.1uF; C_0805_2012Metric
D14: SP0503BAHT; SOT-143
J11: USB_B_Micro; USB_Micro-B_Molex-105017-0001
R52: 1k; R_0805_2012Metric
R53: 22.1k; R_0805_2012Metric
R54: 47.5k; R_0805_2012Metric
U15: CP2102N-A01-GQFN24; QFN-24-1EP_4x4mm_P0.5mm_EP2.6x2.6mm

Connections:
+3V3: C43.1, C44.1, R52.1, U15.5 (VIO), U15.6 (VDD), U15.7 (REGIN); also elsewhere on the board
/USART3_RX: U15.21 (TXD); also elsewhere on the board
/USART3_TX: U15.20 (RXD); also elsewhere on the board
GND: C43.2, C44.2, D14.1 (A), J11.5 (GND), J11.6 (Shield), R54.2, U15.2 (GND), U15.25 (GND); also elsewhere on the board
unnamed: D14.2 (K), J11.1 (VBUS), R53.2
unnamed: D14.3 (K), J11.2 (D-), U15.4 (D-)
unnamed: D14.4 (K), J11.3 (D+), U15.3 (D+)
unnamed: R52.2, U15.9 (~RSTb)
unnamed: R53.1, R54.1, U15.8 (VBUS)

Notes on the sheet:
The microcontroller should have Rx connected to UART_TX and Tx connected to UART_RX
